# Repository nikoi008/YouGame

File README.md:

# YouGame!

## What is it? 
YouGame is a handheld device designed for making games using the tft adruino library!

## Features
12 Buttons -- 10 normal push buttons and 2 shoulder trigger style buttons  
320x240 LCD screen  
SD card slot to store the games on an sd card  
ESP32 S3 as the brains  

## Why was this made?  
I mainly decided to do this since I had an old raspberry pi screen that i thought was fried. Since i didn't have my pi on me, I decided to use my esp32 to see if it was. After a while of figuring out which pin goes where, i finally managed to turn on the backlight, and then got images displaying on it! After that i had the idea to turn it into something more than just making it work, so I decided to use it for my second ever hardware project. Along the way I figured out how to use SD card modules, used an expansion board which connects all the buttons together, and learned a lot about hardware all together!  

## Building instructions

Its easiest to start with smallest first, so here is how it will go.  

### Sd card module and triggers
The sd card module and the triggers are going to be under the board, so make sure they are connected the right way round

### MCP2017 Expansion board
Get your soldering iron out because thisll have to be hand soldered

### Headers and buttons  
Headers and buttons are all through hole components so it shouldn't be too challenging to solder them through
## BOM

| Item | Qty | Price (USD) | Link |
|---|---|---|---|
| 2.4" Touch Screen SPI TFT LCD | 1 | $10.24 | [Link](https://www.aliexpress.com/item/1005005770033042.html) |
|2x40 Breakable Pin Header 2.54mm Male (10pcs) | 1 | $2.05 | [Link](https://a.aliexpress.com/_EJZPzXy) |
| Momentary Tactile Push Button 6x6x5 Right Angle (20pcs) | 1 | $1.74 | [Link](https://www.aliexpress.com/item/1005006384754591.html) |
| 12x12mm Panel Tactile Switch, H6.5mm (10pcs) — shoulder buttons | 1 | $1.60 | [Link](https://www.aliexpress.com/item/1005006164609617.html) |
| TF Micro SD Card Module (SPI) | 1 | $0.90 | [Link](https://www.aliexpress.com/item/1005005302035188.html) |
| Female Pin Header Socket Gold Plated 15-Pin (10pcs) | 1 | $3.70 | [Link](https://www.aliexpress.com/item/1005003610333849.html) |
| ESP32 WiFi Bluetooth Dev Board Type-C CH340 | 1 | $5.59 | [Link](https://www.aliexpress.com/item/1005008771142129.html) |
| PCB fabrication | 1 | $11.45 | jlcbcp.com  |
| MCP2017-SS expansion baord | 1 | 1.84 | https://www.aliexpress.com/item/1005010450787157.html?mp=1 |

**Total:** $39.1

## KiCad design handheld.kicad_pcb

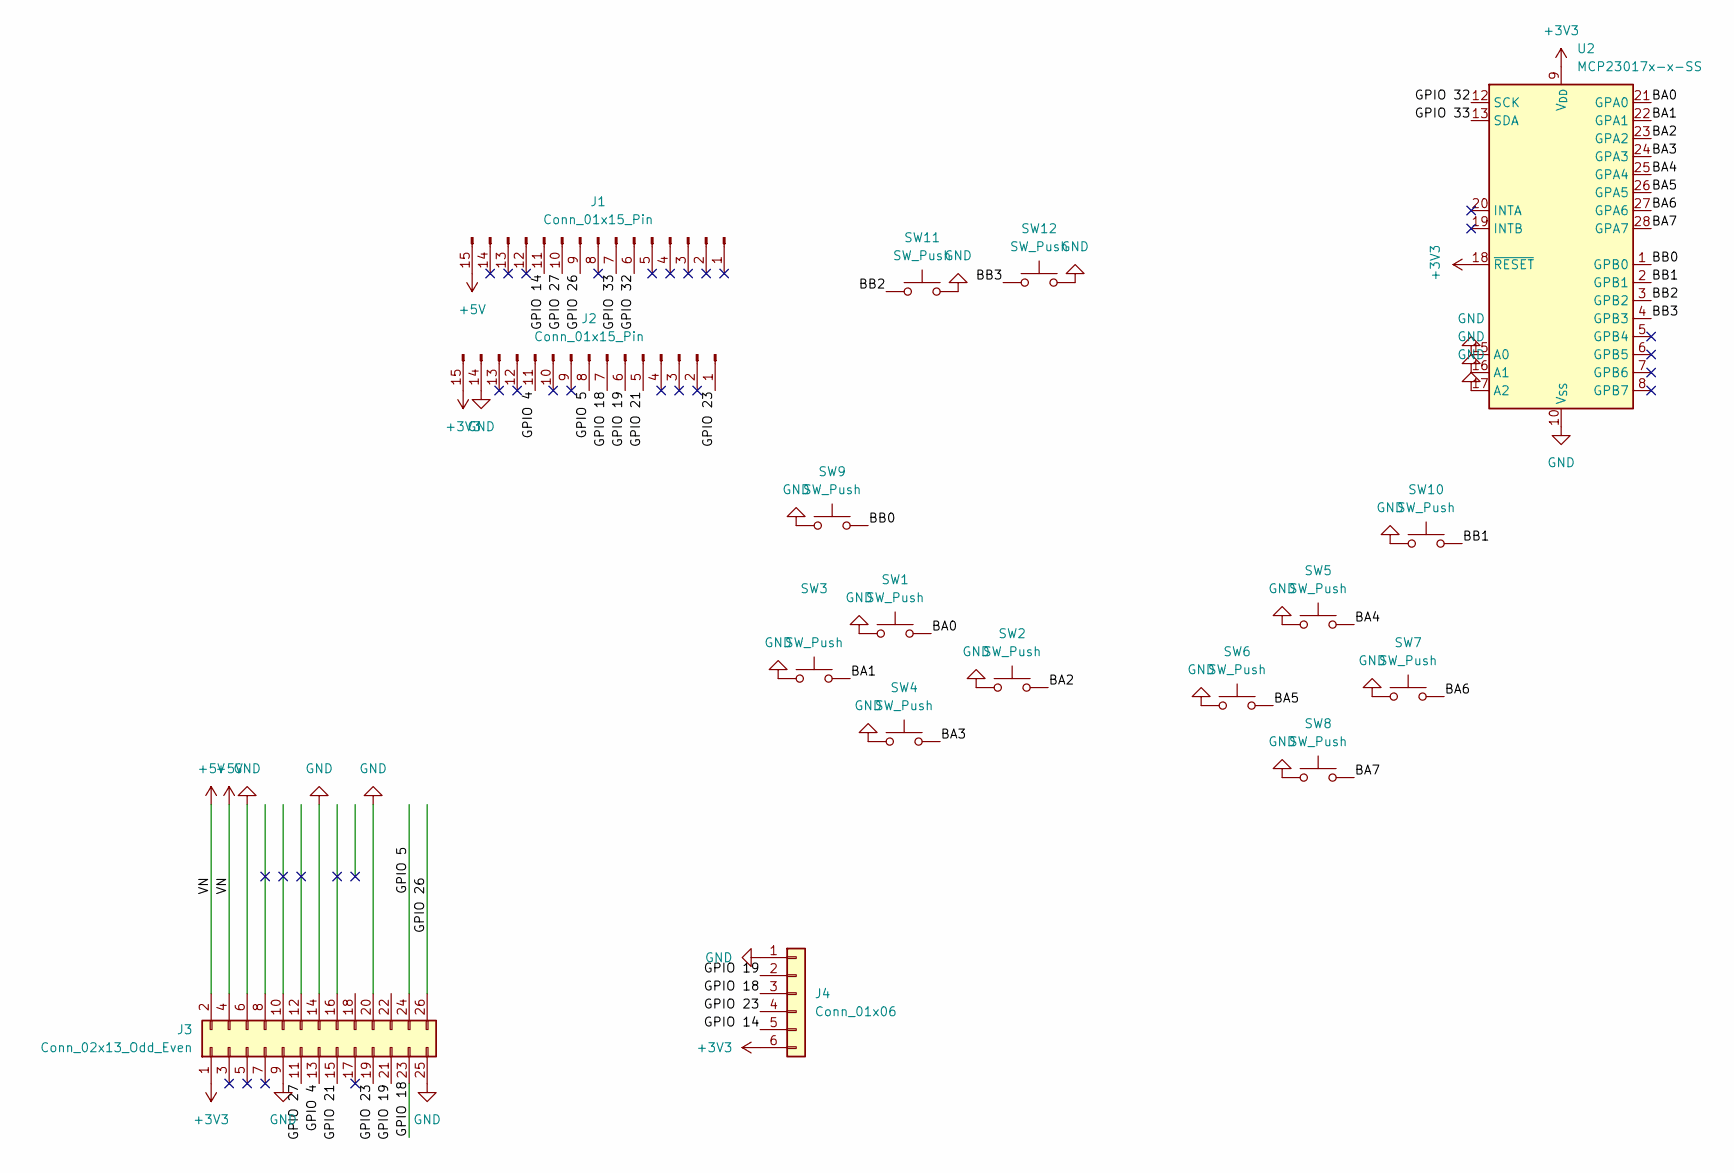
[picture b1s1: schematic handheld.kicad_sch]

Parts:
J1, J2: Conn_01x15_Pin; PinSocket_1x15_P2.54mm_Vertical
J3: Conn_02x13_Odd_Even; PinHeader_2x13_P2.54mm_Vertical
J4: Conn_01x06; PinHeader_1x06_P2.54mm_Vertical
SW1, SW2, SW3, SW4, SW5, SW6, SW7, SW8, SW9, SW10: SW_Push; SW_PUSH_6mm
SW11, SW12: SW_Push; SW_Tactile_SKHH_Angled
U2: MCP23017x-x-SS; SSOP-28_5.3x10.2mm_P0.65mm

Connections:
+3V3: J2.15, J3.1, J4.6, U2.9 (V_{DD}), U2.18 (~RESET)
+5V: J1.15, J3.2, J3.4
/BA0: SW1.2, U2.21 (GPA0)
/BA1: SW3.2, U2.22 (GPA1)
/BA2: SW2.2, U2.23 (GPA2)
/BA3: SW4.2, U2.24 (GPA3)
/BA4: SW5.2, U2.25 (GPA4)
/BA5: SW6.2, U2.26 (GPA5)
/BA6: SW7.2, U2.27 (GPA6)
/BA7: SW8.2, U2.28 (GPA7)
/BB0: SW9.2, U2.1 (GPB0)
/BB1: SW10.2, U2.2 (GPB1)
/BB2: SW11.1, U2.3 (GPB2)
/BB3: SW12.1, U2.4 (GPB3)
/GPIO 4: J2.11, J3.13
/GPIO 5: J2.8, J3.24
/GPIO 14: J1.11, J4.5
/GPIO 18: J2.7, J3.23, J4.3
/GPIO 19: J2.6, J3.21, J4.2
/GPIO 21: J2.5, J3.15
/GPIO 23: J2.1, J3.19, J4.4
/GPIO 26: J1.9, J3.26
/GPIO 27: J1.10, J3.11
/GPIO 32: J1.6, U2.12 (SCK)
/GPIO 33: J1.7, U2.13 (SDA)
GND: J2.14, J3.6, J3.9, J3.14, J3.20, J3.25, J4.1, SW1.1, SW2.1, SW3.1, SW4.1, SW5.1, SW6.1, SW7.1, SW8.1, SW9.1, SW10.1, SW11.2, SW12.2, U2.10 (V_{SS}), U2.15 (A0), U2.16 (A1), U2.17 (A2)

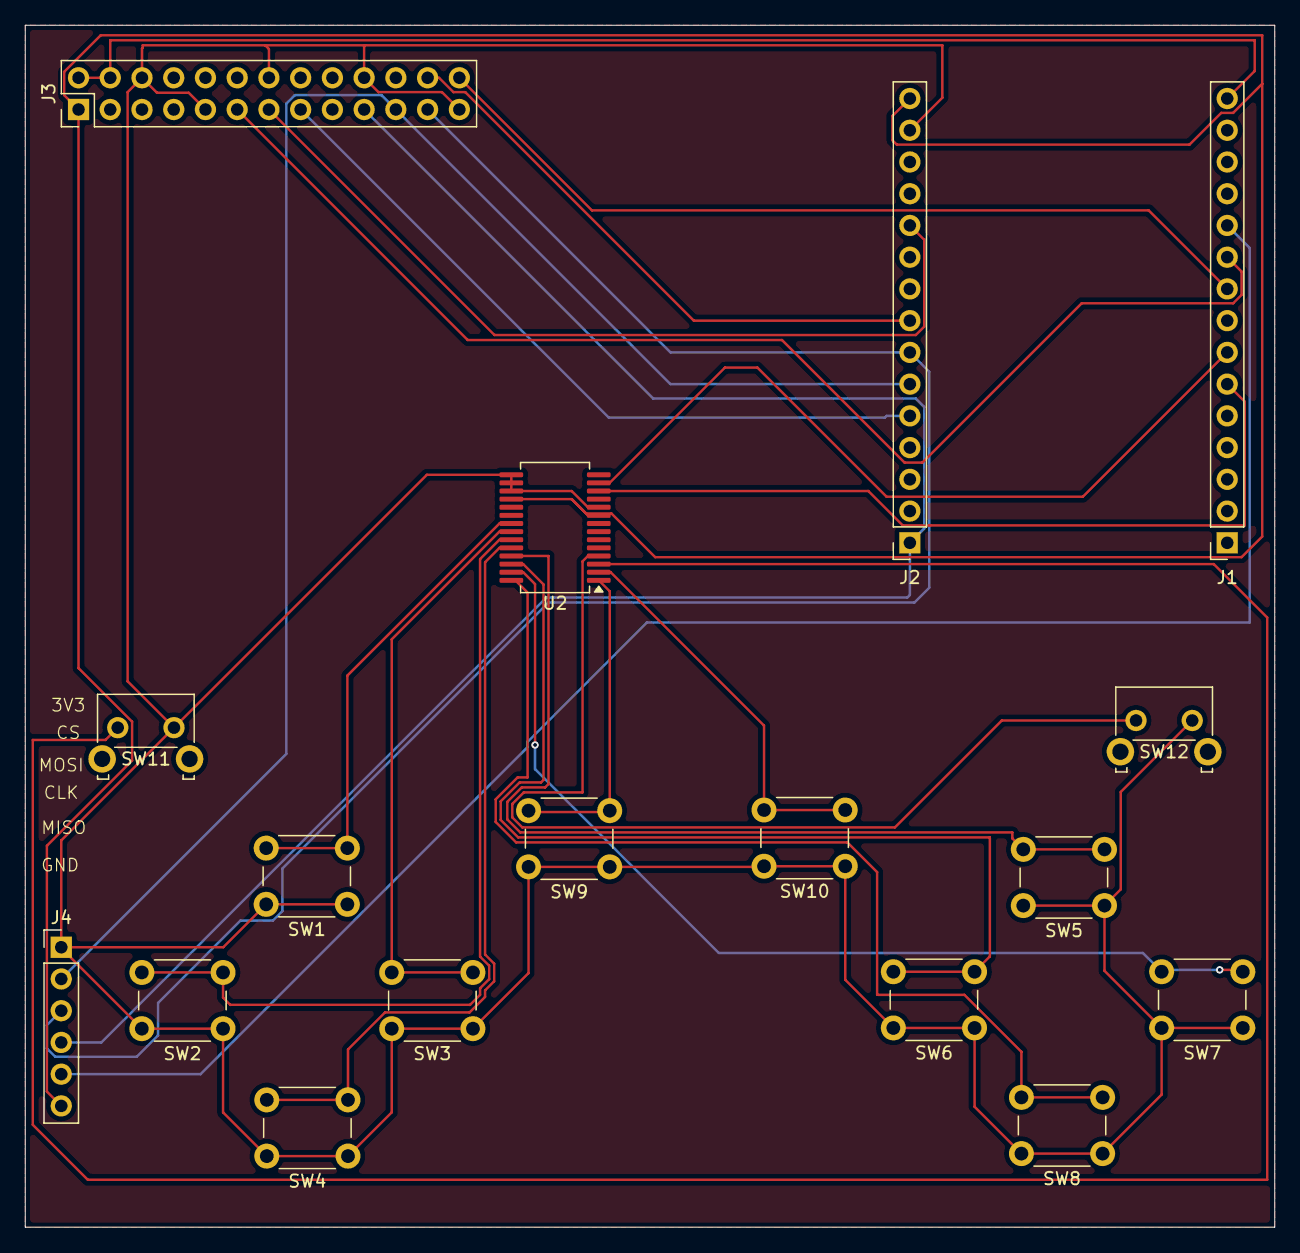
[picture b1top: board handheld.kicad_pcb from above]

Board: 2 copper layers, 100.0 x 96.2 mm, 17 parts (0 on the bottom side), 26 nets.

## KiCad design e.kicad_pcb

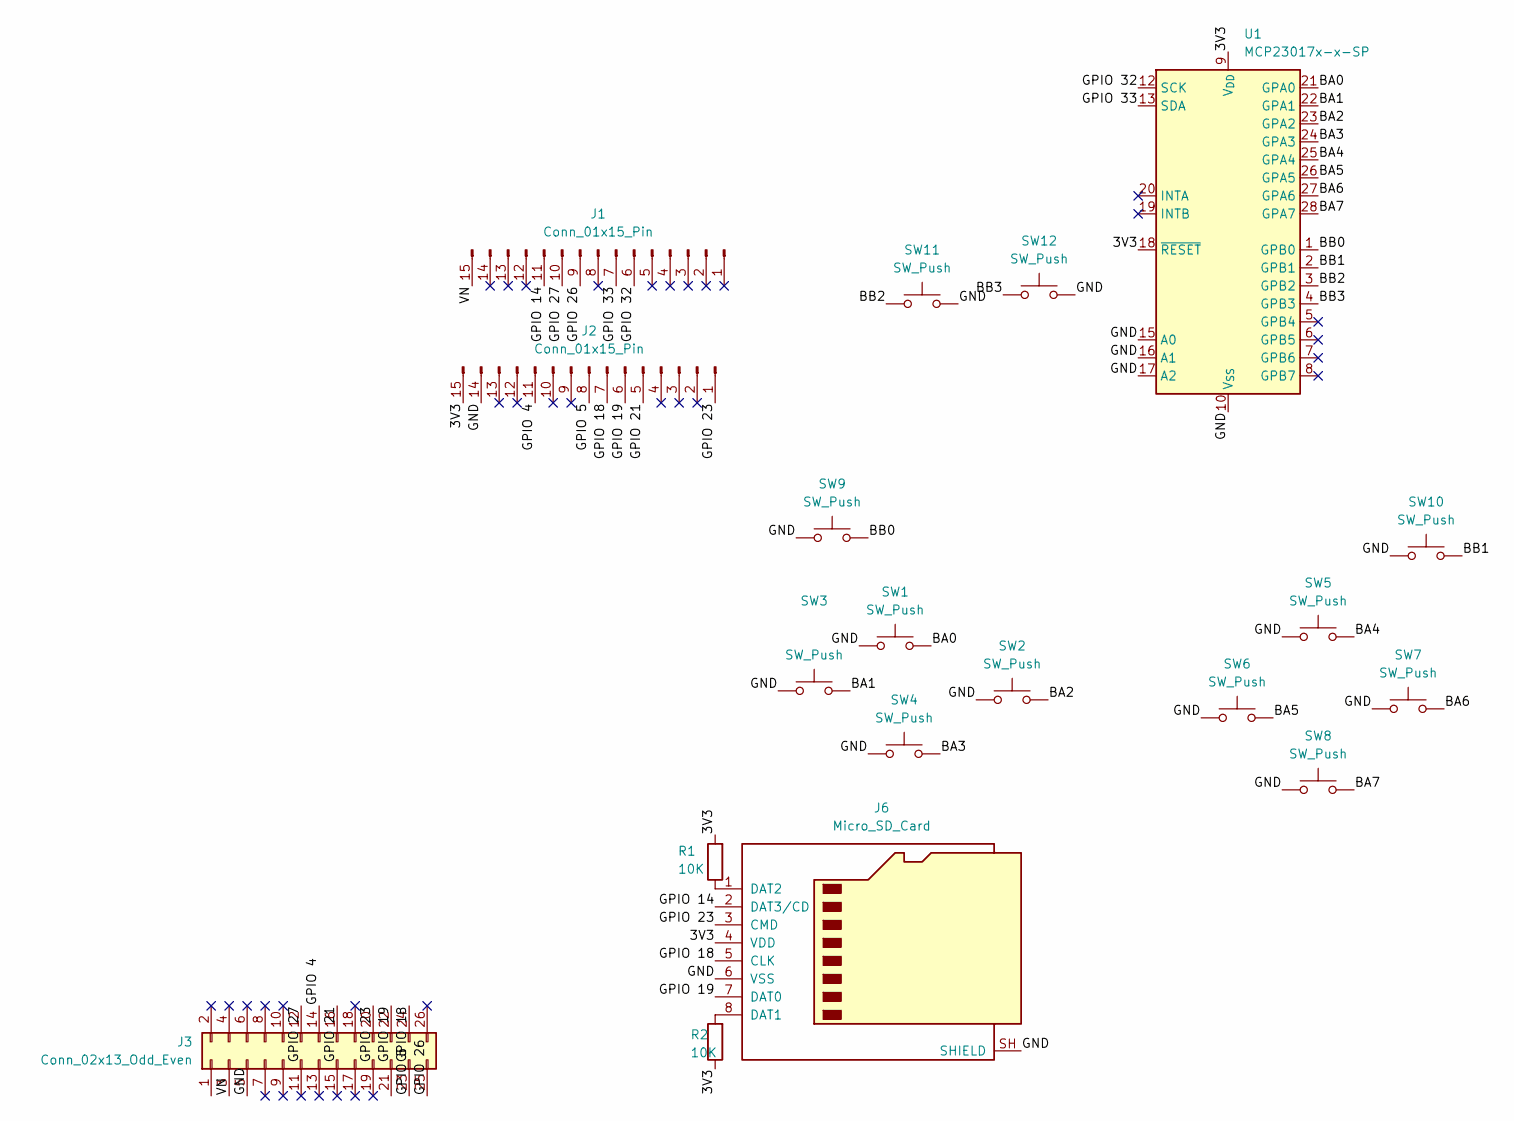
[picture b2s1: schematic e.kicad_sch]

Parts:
J1, J2: Conn_01x15_Pin; PinSocket_1x15_P2.54mm_Vertical
J3: Conn_02x13_Odd_Even; PinSocket_2x13_P2.54mm_Vertical
J6: Micro_SD_Card; microSD_HC_Wuerth_693072010801
R1, R2: 10K; R_0805_2012Metric
SW1, SW2, SW3, SW4, SW5, SW6, SW7, SW8, SW9, SW10: SW_Push; SW_PUSH_6mm
SW11, SW12: SW_Push; SW_Tactile_SKHH_Angled
U1: MCP23017x-x-SP; DIP-28_W7.62mm

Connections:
/3V3: J2.15, J6.4 (VDD), R1.2, R2.1, U1.9 (V_{DD}), U1.18 (~RESET)
/BA0: SW1.2, U1.21 (GPA0)
/BA1: SW3.2, U1.22 (GPA1)
/BA2: SW2.2, U1.23 (GPA2)
/BA3: SW4.2, U1.24 (GPA3)
/BA4: SW5.2, U1.25 (GPA4)
/BA5: SW6.2, U1.26 (GPA5)
/BA6: SW7.2, U1.27 (GPA6)
/BA7: SW8.2, U1.28 (GPA7)
/BB0: SW9.2, U1.1 (GPB0)
/BB1: SW10.2, U1.2 (GPB1)
/BB2: SW11.1, U1.3 (GPB2)
/BB3: SW12.1, U1.4 (GPB3)
/GND: J2.14, J3.5, J6.6 (VSS), J6.SH (SHIELD), SW1.1, SW2.1, SW3.1, SW4.1, SW5.1, SW6.1, SW7.1, SW8.1, SW9.1, SW10.1, SW11.2, SW12.2, U1.10 (V_{SS}), U1.15 (A0), U1.16 (A1), U1.17 (A2)
/GPIO 4: J2.11, J3.14
/GPIO 5: J2.8, J3.23
/GPIO 14: J1.11, J6.2 (DAT3/CD)
/GPIO 18: J2.7, J3.24, J6.5 (CLK)
/GPIO 19: J2.6, J3.22, J6.7 (DAT0)
/GPIO 21: J2.5, J3.16
/GPIO 23: J2.1, J3.20, J6.3 (CMD)
/GPIO 26: J1.9, J3.25
/GPIO 27: J1.10, J3.12
/GPIO 32: J1.6, U1.12 (SCK)
/GPIO 33: J1.7, U1.13 (SDA)
/VN: J1.15, J3.3
unnamed: J6.8 (DAT1), R2.2
unnamed: J6.1 (DAT2), R1.1

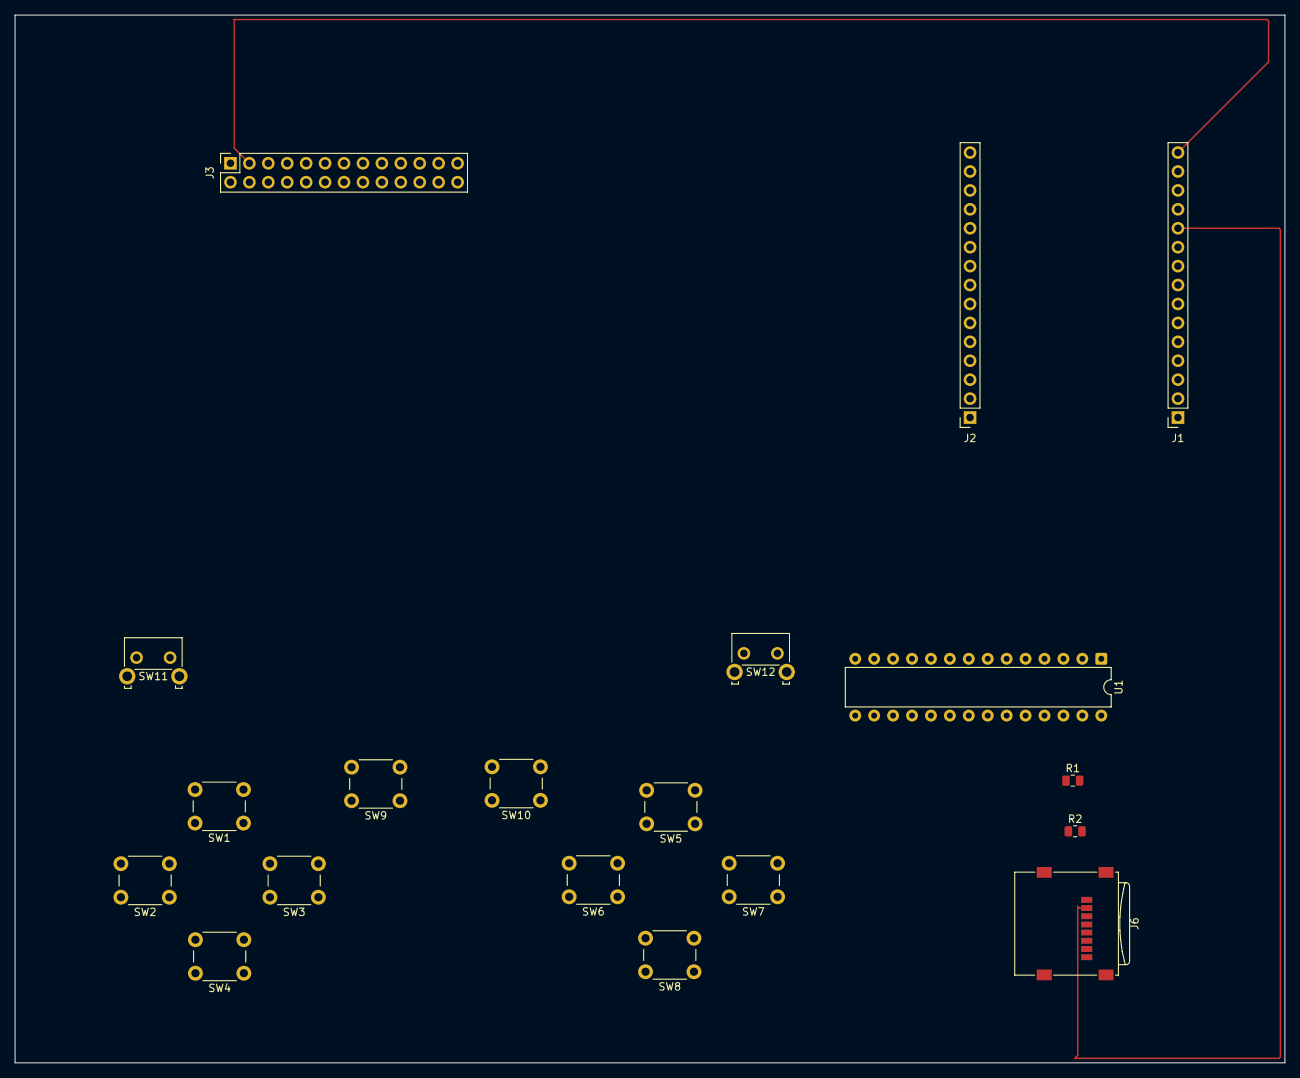
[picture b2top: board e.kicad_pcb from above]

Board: 2 copper layers, 170.4 x 140.6 mm, 19 parts (0 on the bottom side), 28 nets.
